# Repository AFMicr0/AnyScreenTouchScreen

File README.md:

# AnyScreenTouchScreen
ECE 445 Final Project

We have another repository for this project here:
https://github.com/Sakhiyuvio/Any-Screen-to-Touch-Screen

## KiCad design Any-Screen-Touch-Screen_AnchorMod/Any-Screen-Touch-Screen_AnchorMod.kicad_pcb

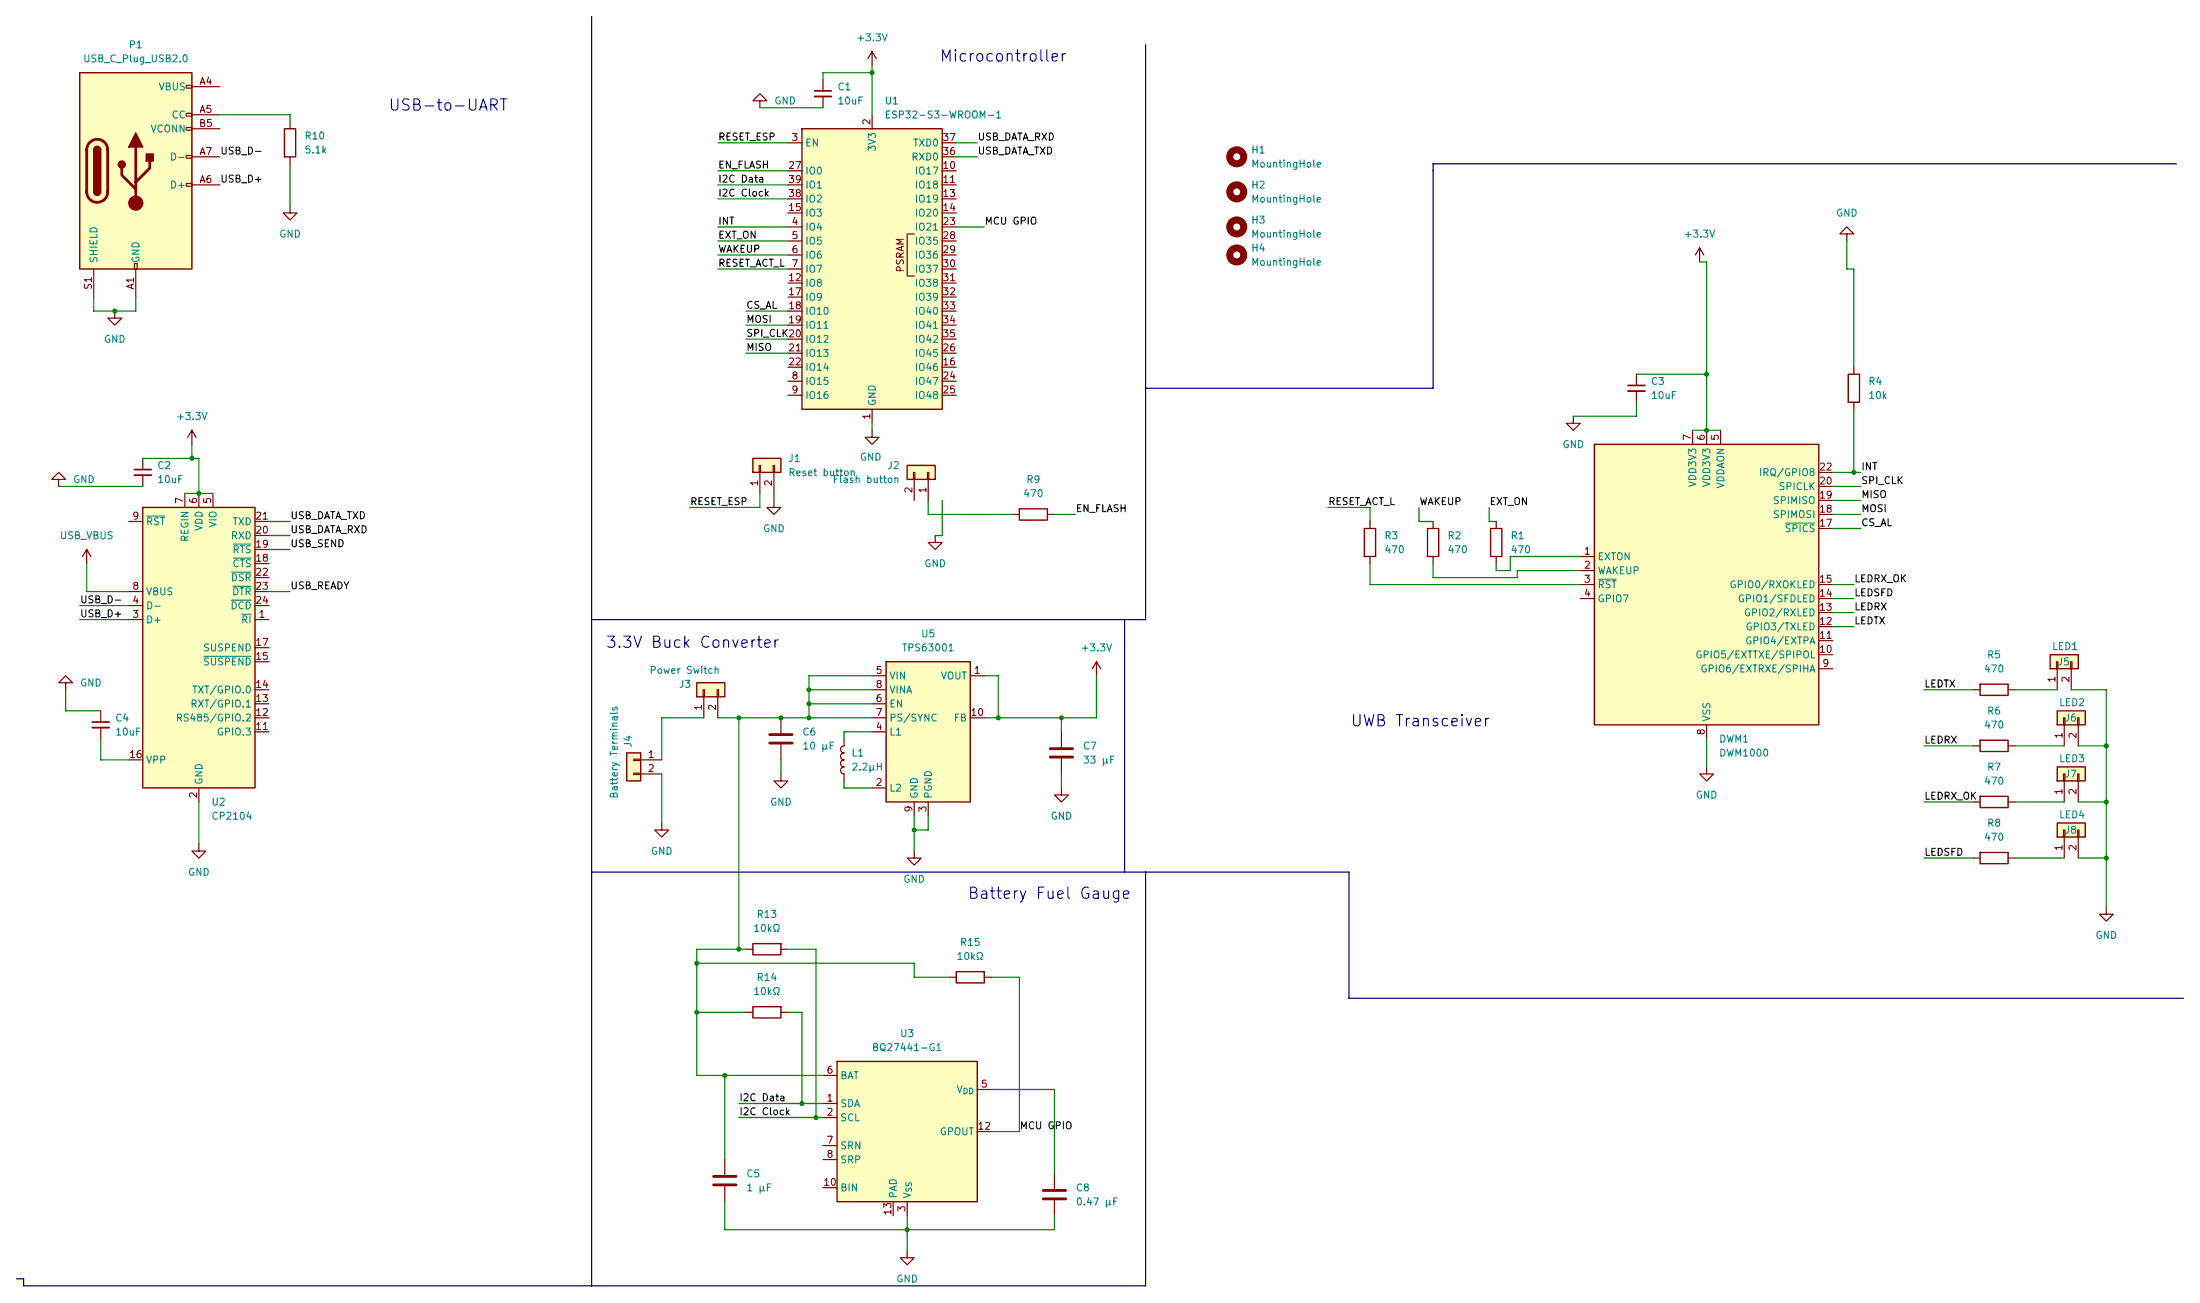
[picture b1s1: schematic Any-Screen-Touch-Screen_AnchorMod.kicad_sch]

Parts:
C1, C2, C3, C4: 10uF; C_0805_2012Metric_Pad1.18x1.45mm_HandSolder
C5: 1 μF; C_0805_2012Metric_Pad1.18x1.45mm_HandSolder
C6: 10 μF; C_0805_2012Metric_Pad1.18x1.45mm_HandSolder
C7: 33 μF; C_0805_2012Metric_Pad1.18x1.45mm_HandSolder
C8: 0.47 μF; C_0805_2012Metric_Pad1.18x1.45mm_HandSolder
DWM1: DWM1000
H1, H2, H3, H4: MountingHole; MountingHole_3.2mm_M3
J1: Reset button; Molex_KK-254_AE-6410-02A_1x02_P2.54mm_Vertical
J2: Flash button; Molex_KK-254_AE-6410-02A_1x02_P2.54mm_Vertical
J3: Power Switch; Molex_KK-254_AE-6410-02A_1x02_P2.54mm_Vertical
J4: Battery Terminals; Molex_KK-254_AE-6410-02A_1x02_P2.54mm_Vertical
J5: LED1; Molex_KK-254_AE-6410-02A_1x02_P2.54mm_Vertical
J6: LED2; Molex_KK-254_AE-6410-02A_1x02_P2.54mm_Vertical
J7: LED3; Molex_KK-254_AE-6410-02A_1x02_P2.54mm_Vertical
J8: LED4; Molex_KK-254_AE-6410-02A_1x02_P2.54mm_Vertical
L1: 2.2μH; IND_MSS5131_COC
P1: USB_C_Plug_USB2.0; USB_C_Plug_Molex_105444
R1, R2, R3, R5, R6, R7, R8, R9: 470; R_0805_2012Metric_Pad1.20x1.40mm_HandSolder
R4: 10k; R_0805_2012Metric_Pad1.20x1.40mm_HandSolder
R10: 5.1k; R_0805_2012Metric_Pad1.20x1.40mm_HandSolder
R13, R14, R15: 10kΩ; R_0805_2012Metric_Pad1.20x1.40mm_HandSolder
U1: ESP32-S3-WROOM-1
U2: CP2104; QFN-24-1EP_4x4mm_P0.5mm_EP2.7x2.7mm_ThermalVias
U3: BQ27441-G1; Texas_S-PDSO-N12
U5: TPS63001; Texas_DRC0010J_ThermalVias

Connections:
+3.3V: C1.1, C2.1, C3.1, C7.1, DWM1.5 (VDDAON), DWM1.6 (VDD3V3), DWM1.7 (VDD3V3), U1.2 (3V3), U2.5 (VIO), U2.6 (VDD), U2.7 (REGIN), U5.1 (VOUT), U5.10 (FB)
/CS_AL: DWM1.17 (~SPICS), U1.18 (IO10)
/EN_FLASH: R9.1, U1.27 (IO0)
/EXT_ON: R1.1, U1.5 (IO5)
/I2C Clock: R13.2, U1.38 (IO2), U3.2 (SCL)
/I2C Data: R14.2, U1.39 (IO1), U3.1 (SDA)
/INT: DWM1.22 (IRQ/GPIO8), R4.2, U1.4 (IO4)
/LEDRX: DWM1.13 (GPIO2/RXLED), R6.2
/LEDRX_OK: DWM1.15 (GPIO0/RXOKLED), R7.2
/LEDSFD: DWM1.14 (GPIO1/SFDLED), R8.2
/LEDTX: DWM1.12 (GPIO3/TXLED), R5.2
/MCU GPIO: R15.2, U1.23 (IO21), U3.12 (GPOUT)
/MISO: DWM1.19 (SPIMISO), U1.21 (IO13)
/MOSI: DWM1.18 (SPIMOSI), U1.19 (IO11)
/RESET_ACT_L: R3.1, U1.7 (IO7)
/RESET_ESP: J1.1, U1.3 (EN)
/SPI_CLK: DWM1.20 (SPICLK), U1.20 (IO12)
/USB_D+: P1.A6 (D+), U2.3 (D+)
/USB_D-: P1.A7 (D-), U2.4 (D-)
/USB_DATA_RXD: U1.37 (TXD0), U2.20 (RXD)
/USB_DATA_TXD: U1.36 (RXD0), U2.21 (TXD)
/USB_READY: U2.23 (~DTR)
/USB_SEND: U2.19 (~RTS)
/WAKEUP: R2.1, U1.6 (IO6)
GND: C1.2, C2.2, C3.2, C4.1, C5.2, C6.1, C7.2, C8.2, DWM1.8 (VSS), DWM1.16 (VSS), DWM1.21 (VSS), DWM1.23 (VSS), DWM1.24 (VSS), J1.2, J4.2, J5.2, J6.2, J7.2, J8.2, P1.A1 (GND), P1.A12 (GND), P1.B1 (GND), P1.B12 (GND), P1.S1 (SHIELD), R4.1, R10.2, U1.1 (GND), U1.40 (GND), U1.41 (GND), U2.2 (GND), U2.25 (GND), U3.3 (V_{SS}), U5.3 (PGND), U5.9 (GND), U5.11 (PGND)
unnamed: DWM1.1 (EXTON), R1.2
unnamed: DWM1.2 (WAKEUP), R2.2
unnamed: DWM1.3 (~RST), R3.2
unnamed: J2.1, R9.2
unnamed: J3.1, J4.1
unnamed: C5.1, C6.2, J3.2, R13.1, R14.1, R15.1, U3.6 (BAT), U5.5 (VIN), U5.6 (EN), U5.7 (PS/SYNC), U5.8 (VINA)
unnamed: J5.1, R5.1
unnamed: J6.1, R6.1
unnamed: J7.1, R7.1
unnamed: J8.1, R8.1
unnamed: P1.A5 (CC), R10.1
unnamed: P1.A4 (VBUS), P1.A9 (VBUS), P1.B4 (VBUS), P1.B9 (VBUS)
unnamed: C4.2, U2.16 (VPP)
unnamed: C8.1, U3.5 (V_{DD})
unnamed: L1.2, U5.4 (L1)
unnamed: L1.1, U5.2 (L2)
USB_VBUS: U2.8 (VBUS)

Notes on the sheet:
USB-to-UART
Microcontroller
3.3V Buck Converter
Battery Fuel Gauge
UWB Transceiver

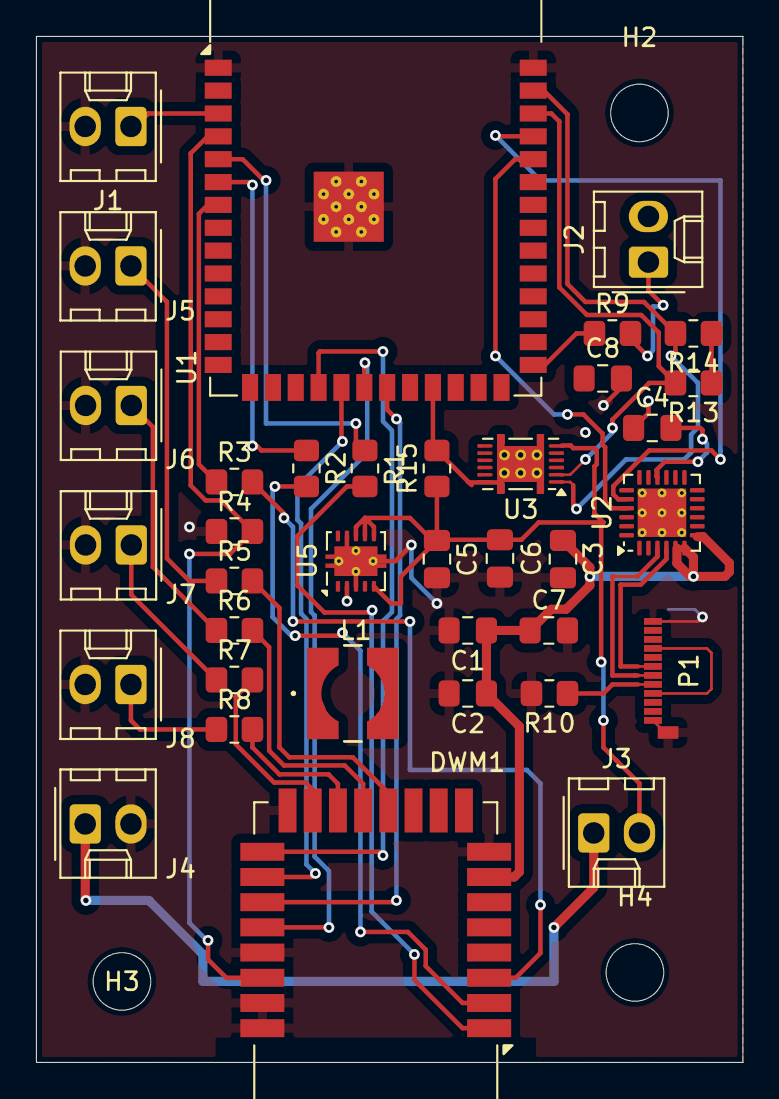
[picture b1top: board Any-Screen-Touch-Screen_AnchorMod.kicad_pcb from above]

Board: 2 copper layers, 39.2 x 57.0 mm, 40 parts (0 on the bottom side), 39 nets.

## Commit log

2024-09-17 Create README.md for notebook
2024-09-17 Create Sakhi Yunalfian
2024-09-25 updated lab notebook and power subsystem schematics
2024-09-25 Update README.md?
2024-09-25 Update README.md again?
2024-09-25 Update README.md 3rd time
2024-09-25 Update README.md 4th times the charm?
2024-09-25 figured out the TOC issue
2024-10-01 updated Notebook and pcb design files
2024-10-01 Anchor Subsystem Schematic Design
2024-10-01 Pen Subsystem Schematic Design
2024-10-03 Updated lab notebook
2024-10-10 Merged power subsystem into pen and anchor schematics, changed input/output devices to pin connectors; also updated lab notebook
2024-10-11 Started PCB layout and organized components
2024-10-11 did most of the PCB routing, updated lab notebook
2024-10-13 update pcb
